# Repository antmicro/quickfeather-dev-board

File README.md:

# QuickFeather Development Board

Copyright (c) 2019-2024 [Antmicro](https://www.antmicro.com)

## Overview

This project contains open hardware design files for the [QuickFeather development board](https://www.quicklogic.com/products/eos-s3/quickfeather-development-kit/) based on the QuickLogic [EOS S3 Sensor Processing Platform](https://www.quicklogic.com/products/eos-s3/).
The design files were created by [Antmicro](https://www.antmicro.com) in cooperation with [QuickLogic](https://www.quicklogic.com/).
The board has been designed to keep compatibility with the [Adafruit Feather](https://learn.adafruit.com/adafruit-feather/feather-specification) ecosystem of evaluation boards.
This allows the user to explore functionalities of the EOS S3 platform.

### Project structure:

The main directory contains the KiCad design files, LICENSE and README.
The remaining files are stored in the following directories:

* ``img`` - contains graphics for this README
* ``doc`` - contains generated schematics and other documentation
* ``lib`` - contains KiCad component library

## Key features

* QuickLogic EOS S3 Processing Platform
* [mCube MC3635](https://www.memsic.com/Public/Uploads/uploadfile/files/20220119/MC3635Datasheet.pdf) accelerometer
* [Infineon DPS310](https://www.infineon.com/dgdl/Infineon-DPS310-DataSheet-v01_01-EN.pdf?fileId=5546d462576f34750157750826c42242) pressure sensor
* [Infineon IM69D130](https://www.infineon.com/dgdl/Infineon-IM69D130-DS-v01_00-EN.pdf?fileId=5546d462602a9dc801607a0e46511a2e) MEMS microphone 
* 16Mbit of on-board [flash memory](https://www.gigadevice.com.cn/Public/Uploads/uploadfile/files/20220714/DS-00086-GD25Q16C-Rev3.2.pdf)
* User button and RGB LED
* Powered from USB or a single Li-Po battery
* Integrated [battery charger](http://ww1.microchip.com/downloads/en/DeviceDoc/20001984g.pdf)
* USB data signals tied to programmable logic
* IO signals break-routed into general purpose pinheads
* Compatible with standard 0.1" breadboards

## Development ecosystem

### Simulation

The board is supported in [Renode](https://renode.io/), the open source simulation framework by Antmicro - you can run a virtual copy of this hardware for software development purposes on your PC. A link to the relevant demo script is provided in Renode's [supported boards section](https://renode.readthedocs.io/en/latest/introduction/supported-boards.html).

## License

This project is licensed under the [CC BY-SA 4.0 DEED](LICENSE) license.

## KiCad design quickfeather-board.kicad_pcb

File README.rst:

==============================
QuickFeather Development Board
==============================

Copyright (c) 2019-2021 `Antmicro <https://www.antmicro.com>`_

.. figure:: img/feather-board.png

Overview
========

This repository contains open hardware design files for the `QuickFeather development board <https://www.quicklogic.com/products/eos-s3/quickfeather-development-kit/>`_ based on the QuickLogic `EOS S3 Sensor Processing Platform <https://www.quicklogic.com/products/eos-s3/>`_.
The design files were created by `Antmicro <https://www.antmicro.com>`_ in cooperation with `QuickLogic <https://www.quicklogic.com/>`_.
The board has been designed to keep compatibility with the `Adafruit Feather <https://learn.adafruit.com/adafruit-feather/feather-specification>`_ ecosystem of evaluation boards.
This allows the user to explore functionalities of the EOS S3 platform.

Key features
------------

* QuickLogic EOS S3 Processing Platform
* `mCube MC3635 <https://mcubemems.com/wp-content/uploads/2019/06/MC3635-Datasheet-APS-048-0044v1.6.pdf>`_ accelerometer
* `Infineon DPS310 <https://www.infineon.com/dgdl/Infineon-DPS310-DataSheet-v01_01-EN.pdf?fileId=5546d462576f34750157750826c42242>`_ pressure sensor
* `Infineon IM69D130 <https://www.infineon.com/dgdl/Infineon-IM69D130-DS-v01_00-EN.pdf?fileId=5546d462602a9dc801607a0e46511a2e>`_ MEMS microphone 
* 16Mbit of on-board `flash memory  <http://www.gigadevice.com/datasheet/gd25q16c/>`_
* User button and RGB LED
* Powered from USB or a single Li-Po battery
* Integrated `battery charger <http://ww1.microchip.com/downloads/en/DeviceDoc/20001984g.pdf>`_
* USB data signals tied to programmable logic
* IO signals break-routed into general purpose pinheads
* Compatible with standard 0.1" breadboards

Layout and dimensions
---------------------

.. figure:: img/feather-layout.png

Development ecosystem
=====================

Simulation
----------

The board is supported in `Renode <https://renode.io/>`_, the open source simulation framework by Antmicro - you can run a virtual copy of this hardware for software development purposes on your PC. A link to the relevant demo script is provided in Renode's `supported boards section <https://renode.readthedocs.io/en/latest/introduction/supported-boards.html>`_.

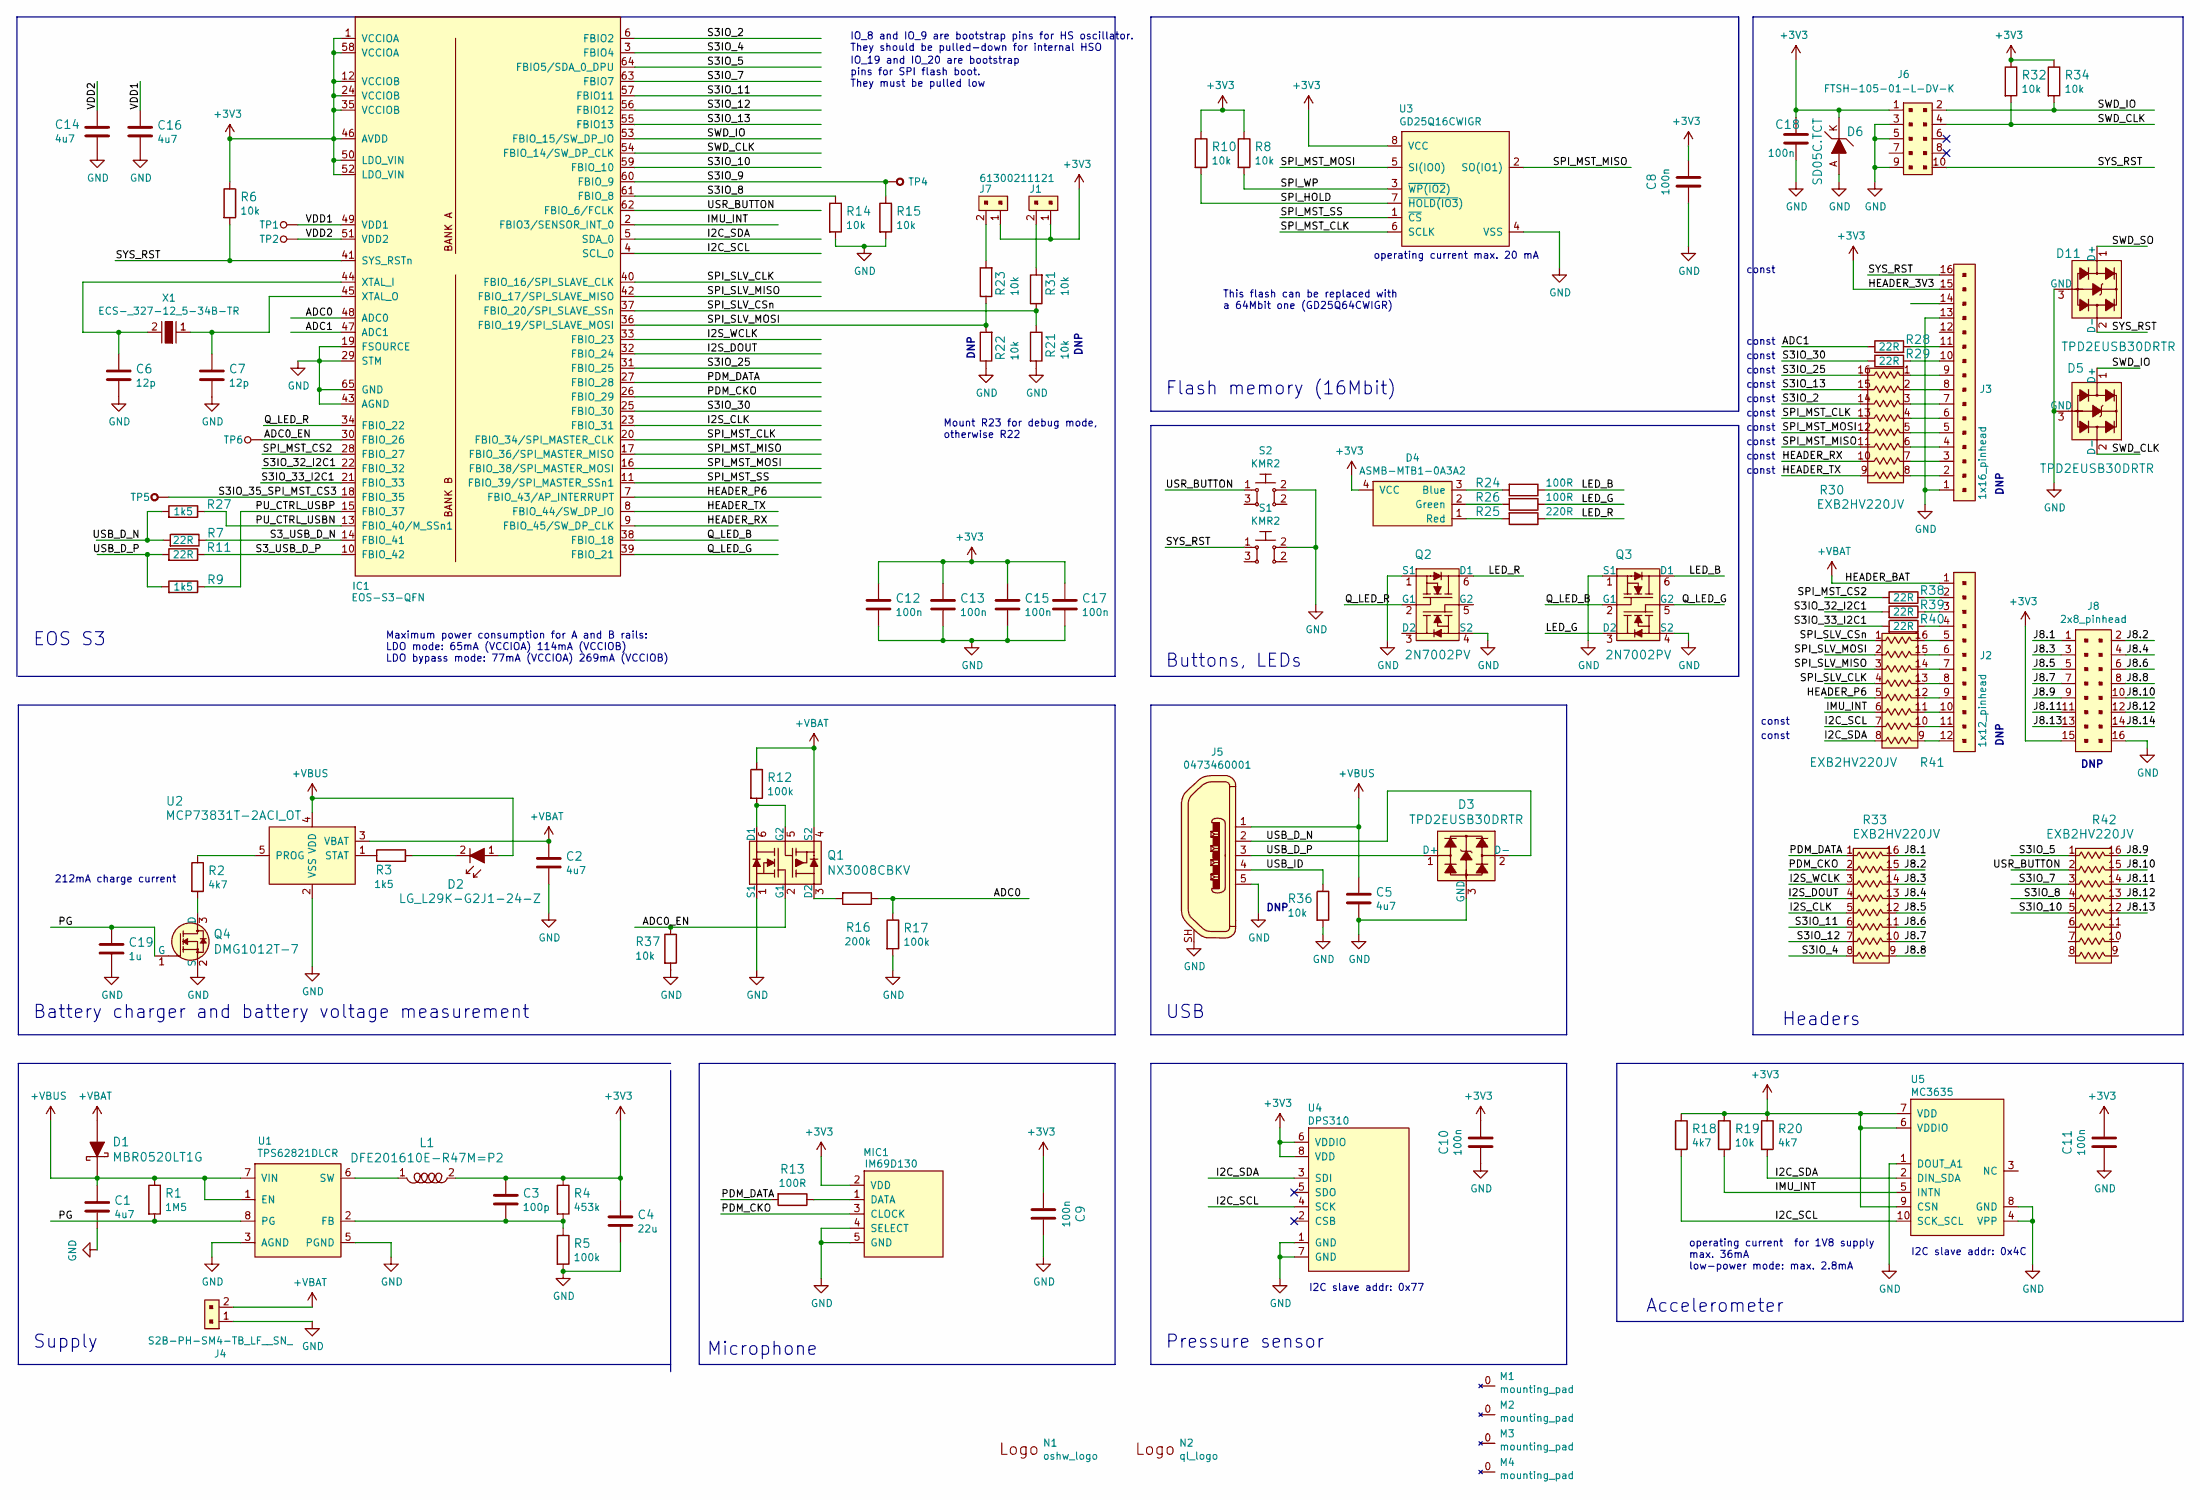
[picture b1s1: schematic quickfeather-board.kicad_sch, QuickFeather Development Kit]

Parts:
C1, C2, C5, C14, C16: C_4u7_0603; 0603-cap; MPN C1608X5R1V475M080AC
C3: C_100p_0402; 0402-cap; MPN 0402N101J500CT
C4: C_22u_0603; 0603-cap; MPN GRM188R60J226MEA0D
C6, C7: C_12p_0402; 0402-cap; MPN CGA2B2C0G1H120J050BA
C8, C9, C10, C11, C12, C13, C15, C17, C18: C_100n_0402_6V3; 0402-cap; MPN 0402X104K6R3CT
C19: C_1u_0402; 0402-cap; MPN C1005X6S1A105K050BC
D1: MBR0520LT1G; SOD-123; MPN MBR0520LT1G
D2: LG_L29K-G2J1-24-Z; LED_0603; MPN LG L29K-G2J1-24-Z
D3, D5, D11: TPD2EUSB30DRTR; SOT-3; MPN TPD2EUSB30DRTR
D4: ASMB-MTB1-0A3A2; LED-PLCC4_3.2x2.8mm_B; MPN UHD1110-FKA
D6: SD05C.TCT; SOD-323-SD05; MPN SD05C.TCT
IC1: EOS-S3-QFN; QFN-64_8.5x8.5_EOS; MPN EOSA1-S-PUN64
J1, J7: 61300211121; PinHeader_1x2_P2.54_Drill0.9mm; MPN 61300211121
J2: 1x12_pinhead; MPN MC34733
J3: 1x16_pinhead; MPN 61301611121
J4: S2B-PH-SM4-TB_LF__SN_; PinHeader_2x1mm_P2mm_SMD_RA; MPN S2B-PH-SM4-TB(LF)(SN)
J5: 0473460001; USB_Micro_B_Female_0473460001; MPN 0473460001
J6: FTSH-105-01-L-DV-K; PinHeader_2x5_P1.27_SMD; MPN FTSH-105-01-L-DV-K
J8: 2x8_pinhead; MPN 2213S-16G
L1: DFE201610E-R47M=P2; 0806; MPN DFE201610E-R47M=P2
M1, M2, M3, M4: mounting_pad; MPAD
MIC1: IM69D130; MPN IM69D130
N1: oshw_logo; oshw-logo
N2: ql_logo; LOGO
Q1: NX3008CBKV; SOT-563; MPN NX3008CBKV
Q2, Q3: 2N7002PV; SOT-563; MPN 2N7002PV
Q4: DMG1012T-7; SOT-523; MPN DMG1012T-7
R1: R_1M5_0402; 0402-res; MPN MCWR04W1504FTL
R2, R18, R20: R_4k7_0402; 0402-res; MPN ERJ2GEJ472X
R3, R9, R27: R_1k5_0402; 0402-res; MPN ERJ2RKF1501X
R4: R_453k_0402; 0402-res; MPN CRCW0402453KFKED
R5, R12, R17: R_100k_0402; 0402-res; MPN CRCW0402100KFKEDHP
R6, R8, R10, R14, R15, R19, R21, R22, R23, R31, R32, R34, R36, R37: R_10k_0402; 0402-res; MPN CRCW040210K0FKEDHP
R7, R11, R28, R29, R38, R39, R40: R_22R_0402; 0402-res; MPN CRCW040222R0FKED
R13, R24, R26: R_100R_0402; 0402-res; MPN CR0402-FX-1000GLF
R16: R_200k_0402; 0402-res; MPN RC0402FR-07200KL
R25: R_220R_0402; 0402-res; MPN RMCF0402JT220R
R30, R33, R41, R42: EXB2HV220JV; R_Array_Convex_8x0602; MPN EXB2HV220JV
S1, S2: KMR2; SW_SPST_4.2x2.8; MPN KMR211NGLFS
TP1, TP2, TP6: TP_SMD1MM; Testpoint_smd_1mm; MPN N/A
TP4, TP5: TP_THT; Testpoint_THT_Drill0.9mm; MPN N/A
U1: TPS62821DLCR; QFN-8_2x1mm; MPN TPS62821DLCR
U2: MCP73831T-2ACI_OT; SOT-753; MPN MCP73831T-2ACI/OT
U3: GD25Q16CWIGR; GD25Q16CWIG; MPN GD25Q16CWIGR
U4: DPS310; PG-VLGA-8-2; MPN DPS310
U5: MC3635; MPN MC3635
X1: ECS-_327-12_5-34B-TR; SMD-2_3.2x1.5mm; MPN ECS-.327-12.5-34B-TR

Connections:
+3V3: C3.1, C4.1, C8.1, C9.2, C10.1, C11.1, C12.1, C13.1, C15.1, C17.1, C18.1, D4.4 (VCC), D6.K, IC1.1 (VCCIOA), IC1.12 (VCCIOB), IC1.24 (VCCIOB), IC1.35 (VCCIOB), IC1.46 (AVDD), IC1.50 (LDO_VIN), IC1.52 (LDO_VIN), IC1.58 (VCCIOA), J1.1, J3.15, J6.1, J7.1, J8.15, L1.2, MIC1.2 (VDD), R4.1, R6.1, R8.1, R10.1, R18.1, R19.1, R20.1, R32.1, R34.1, U3.8 (VCC), U4.6 (VDDIO), U4.8 (VDD), U5.6 (VDDIO), U5.7 (VDD), U5.9 (CSN)
+VBAT: C2.1, D1.A, J2.1, J4.2, Q1.4 (S2), R12.1, U2.3 (VBAT)
+VBUS: C1.1, C5.1, D1.K, D2.1, J5.1, R1.1, U1.1 (EN), U1.7 (VIN), U2.4 (VDD)
/ADC0: IC1.48 (ADC0), R16.1, R17.1
/ADC0_EN: IC1.30 (FBIO_26), Q1.2 (G1), R37.1, TP6.1
/ADC1: IC1.47 (ADC1), R28.1
/HEADER_P6: IC1.7 (FBIO_43/AP_INTERRUPT), R41.5
/HEADER_RX: IC1.9 (FBIO_45/SW_DP_CLK), R30.10
/HEADER_TX: IC1.8 (FBIO_44/SW_DP_IO), R30.9
/I2C_SCL: IC1.4 (SCL_0), R18.2, R41.7, U4.4 (SCK), U5.10 (SCK_SCL)
/I2C_SDA: IC1.5 (SDA_0), R20.2, R41.8, U4.3 (SDI), U5.2 (DIN_SDA)
/I2S_CLK: IC1.23 (FBIO_31), R33.5
/I2S_DOUT: IC1.32 (FBIO_24), R33.4
/I2S_WCLK: IC1.33 (FBIO_23), R33.3
/IMU_INT: IC1.2 (FBIO3/SENSOR_INT_0), R19.2, R41.6, U5.5 (INTN)
/J8.1: J8.1, R33.16
/J8.2: J8.2, R33.15
/J8.3: J8.3, R33.14
/J8.4: J8.4, R33.13
/J8.5: J8.5, R33.12
/J8.6: J8.6, R33.11
/J8.7: J8.7, R33.10
/J8.8: J8.8, R33.9
/J8.9: J8.9, R42.16
/J8.10: J8.10, R42.15
/J8.11: J8.11, R42.14
/J8.12: J8.12, R42.13
/J8.13: J8.13, R42.12
/J8.14: J8.14
/LED_B: Q3.6 (D1), R24.1
/LED_G: Q3.3 (D2), R26.1
/LED_R: Q2.6 (D1), R25.1
/PDM_CKO: IC1.26 (FBIO_29), MIC1.3 (CLOCK), R33.2
/PDM_DATA: IC1.27 (FBIO_28), R13.2, R33.1
/PG: C19.1, Q4.1 (G), R1.2, U1.8 (PG)
/PU_CTRL_USBN: IC1.13 (FBIO_40/M_SSn1), R27.1
/PU_CTRL_USBP: IC1.15 (FBIO_37), R9.1
/Q_LED_B: IC1.38 (FBIO_18), Q3.2 (G1)
/Q_LED_G: IC1.39 (FBIO_21), Q3.5 (G2)
/Q_LED_R: IC1.34 (FBIO_22), Q2.2 (G1)
/S3IO_2: IC1.6 (FBIO2), R30.14
/S3IO_4: IC1.3 (FBIO4), R33.8
/S3IO_5: IC1.64 (FBIO5/SDA_0_DPU), R42.1
/S3IO_7: IC1.63 (FBIO7), R42.3
/S3IO_8: IC1.61 (FBIO_8), R14.1, R42.4
/S3IO_9: IC1.60 (FBIO_9), R15.1, TP4.1
/S3IO_10: IC1.59 (FBIO_10), R42.5
/S3IO_11: IC1.57 (FBIO11), R33.6
/S3IO_12: IC1.56 (FBIO12), R33.7
/S3IO_13: IC1.55 (FBIO13), R30.15
/S3IO_25: IC1.31 (FBIO_25), R30.16
/S3IO_30: IC1.25 (FBIO_30), R29.1
/S3IO_32_I2C1: IC1.22 (FBIO_32), R39.2
/S3IO_33_I2C1: IC1.21 (FBIO_33), R40.2
/S3IO_35_SPI_MST_CS3: IC1.18 (FBIO_35), TP5.1
/S3_USB_D_N: IC1.14 (FBIO_41), R7.1
/S3_USB_D_P: IC1.10 (FBIO_42), R11.1
/SPI_HOLD: R10.2, U3.7 (~HOLD(IO3))
/SPI_MST_CLK: IC1.20 (FBIO_34/SPI_MASTER_CLK), R30.13, U3.6 (SCLK)
/SPI_MST_CS2: IC1.28 (FBIO_27), R38.2
/SPI_MST_MISO: IC1.17 (FBIO_36/SPI_MASTER_MISO), R30.11, U3.2 (SO(IO1))
/SPI_MST_MOSI: IC1.16 (FBIO_38/SPI_MASTER_MOSI), R30.12, U3.5 (SI(IO0))
/SPI_MST_SS: IC1.11 (FBIO_39/SPI_MASTER_SSn1), U3.1 (~CS)
/SPI_SLV_CLK: IC1.40 (FBIO_16/SPI_SLAVE_CLK), R41.4
/SPI_SLV_CSn: IC1.37 (FBIO_20/SPI_SLAVE_SSn), R21.1, R31.1, R41.1
/SPI_SLV_MISO: IC1.42 (FBIO_17/SPI_SLAVE_MISO), R41.3
/SPI_SLV_MOSI: IC1.36 (FBIO_19/SPI_SLAVE_MOSI), R22.2, R23.1, R41.2
/SPI_WP: R8.2, U3.3 (~WP(IO2))
/SWD_CLK: D5.2 (D-), IC1.54 (FBIO_14/SW_DP_CLK), J6.4, R32.2
/SWD_IO: D5.1 (D+), IC1.53 (FBIO_15/SW_DP_IO), J6.2, R34.2
/SWD_SO: D11.1 (D+)
/SYS_RST: D11.2 (D-), IC1.41 (SYS_RSTn), J3.16, J6.10, R6.2, S1.1
/USB_D_N: D3.2 (D-), J5.2, R7.2, R27.2
/USB_D_P: D3.1 (D+), J5.3, R9.2, R11.2
/USB_ID: J5.4, R36.1
/USR_BUTTON: IC1.62 (FBIO_6/FCLK), R42.2, S2.1
/VDD1: C16.1, IC1.49 (VDD1), TP1.1
/VDD2: C14.1, IC1.51 (VDD2), TP2.1
GND: C1.2, C2.2, C4.2, C5.2, C6.2, C7.2, C8.2, C9.1, C10.2, C11.2, C12.2, C13.2, C14.2, C15.2, C16.2, C17.2, C18.2, C19.2, D3.3 (GND), D5.3 (GND), D6.A, D11.3 (GND), IC1.19 (FSOURCE), IC1.29 (STM), IC1.43 (AGND), IC1.65 (GND), J3.1, J3.13, J4.1, J5.5, J5.SH, J6.3, J6.5, J6.9, J8.16, MIC1.4 (SELECT), MIC1.5 (GND), Q1.1 (S1), Q2.1 (S1), Q2.4 (S2), Q3.1 (S1), Q3.4 (S2), Q4.2 (S), R5.2, R14.2, R15.2, R17.2, R21.2, R22.1, R36.2, R37.2, S1.2, S2.2, U1.3 (AGND), U1.5 (PGND), U2.2 (VSS), U3.4 (VSS), U4.1 (GND), U4.7 (GND), U5.1 (DOUT_A1), U5.4 (VPP), U5.8 (GND)
unnamed: C3.2, R4.2, R5.1, U1.2 (FB)
unnamed: C6.1, IC1.44 (XTAL_I), X1.2
unnamed: C7.1, IC1.45 (XTAL_O), X1.1
unnamed: D2.2, R3.1
unnamed: D4.1 (Red), R25.2
unnamed: D4.2 (Green), R26.2
unnamed: D4.3 (Blue), R24.2
unnamed: J1.2, R31.2
unnamed: J2.2, R38.1
unnamed: J2.3, R39.1
unnamed: J2.4, R40.1
unnamed: J2.5, R41.16
unnamed: J2.6, R41.15
unnamed: J2.7, R41.14
unnamed: J2.8, R41.13
unnamed: J2.9, R41.12
unnamed: J2.10, R41.11
unnamed: J2.11, R41.10
unnamed: J2.12, R41.9
unnamed: J3.2, R30.8
unnamed: J3.3, R30.7
unnamed: J3.4, R30.6
unnamed: J3.5, R30.5
unnamed: J3.6, R30.4
unnamed: J3.7, R30.3
unnamed: J3.8, R30.2
unnamed: J3.9, R30.1
unnamed: J3.10, R29.2
unnamed: J3.11, R28.2
unnamed: J7.2, R23.2
unnamed: L1.1, U1.6 (SW)
unnamed: MIC1.1 (DATA), R13.1
unnamed: Q1.3 (D2), R16.2
unnamed: Q1.5 (G2), Q1.6 (D1), R12.2
unnamed: Q4.3 (D), R2.2
unnamed: R2.1, U2.5 (PROG)
unnamed: R3.2, U2.1 (STAT)

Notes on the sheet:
Battery charger and battery voltage measurement
const
Pressure sensor
DNP
operating current max. 20 mA
USB
IO_19 and IO_20 are bootstrap pins for SPI flash boot. They must be pulled low
Supply
Microphone
Headers
This flash can be replaced with a 64Mbit one (GD25Q64CWIGR)
212mA charge current
EOS S3
I2C slave addr: 0x4C
I2C slave addr: 0x77
Flash memory (16Mbit)
Buttons, LEDs
Mount R23 for debug mode, otherwise R22
Maximum power consumption for A and B rails: LDO mode: 65mA (VCCIOA) 114mA (VCCIOB) LDO bypass mode: 77mA (VCCIOA) 269mA (VCCIOB)
IO_8 and IO_9 are bootstrap pins for HS oscillator. They should be pulled-down for internal HSO
Accelerometer
operating current for 1V8 supply max. 36mA low-power mode: max. 2.8mA

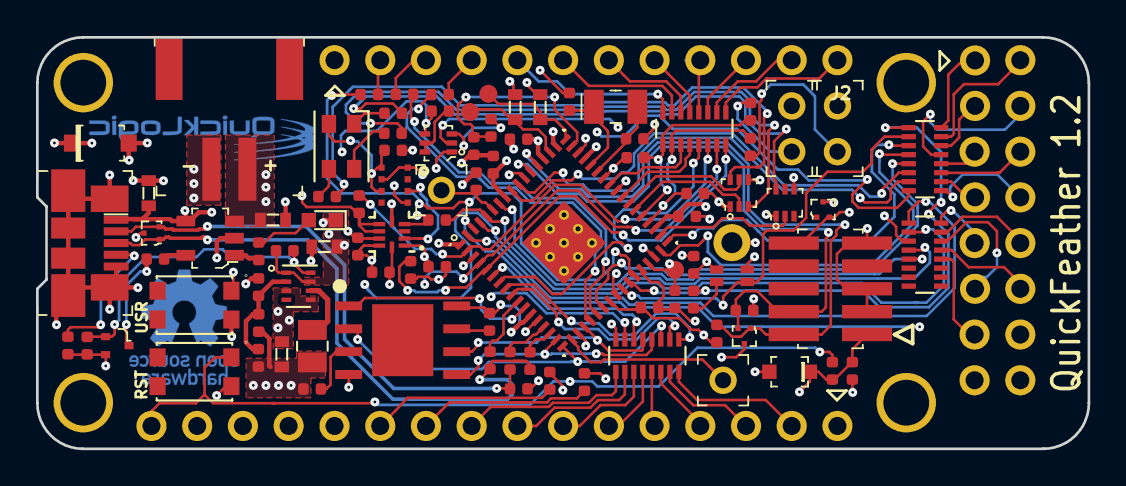
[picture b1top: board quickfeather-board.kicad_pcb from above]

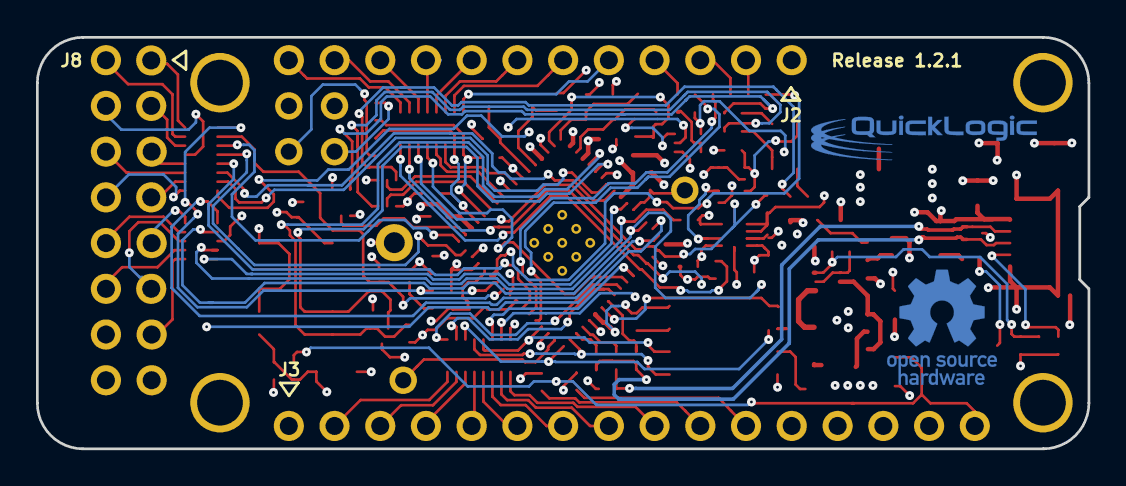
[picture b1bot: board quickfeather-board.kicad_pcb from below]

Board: 4 copper layers, 58.4 x 22.9 mm, 101 parts (2 on the bottom side), 114 nets.

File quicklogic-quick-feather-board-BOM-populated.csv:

Reference,Quantity,Value,Footprint,Manufacturer,MPN,
C1 C14 C16 C2 C5,5,C_4u7_0603,0603-cap,TDK,C1608X5R1V475M080AC,
C10 C11 C12 C13 C15 C17 C18 C8 C9,9,C_100n_0402_6V3,0402-cap,Walsin,0402X104K6R3CT,
C3,1,C_100p_0402,0402-cap,WALSIN,0402N101J500CT,
C4,1,C_22u_0603,0603-cap,MURATA,GRM188R60J226MEA0D,
C6 C7,2,C_12p_0402,0402-cap,TDK,CGA2B2C0G1H120J050BA,
D1,1,MBR0520LT1G,SOD-123,ON Semiconductor,MBR0520LT1G,
D11 D3 D5,3,TPD2EUSB30DRTR,SOT-3,Texas Instruments,TPD2EUSB30DRTR,
D2,1,LG_L29K-G2J1-24-Z,LED_0603,OSRAM Opto Semiconductors Inc.,LG L29K-G2J1-24-Z,
D4,1,ASMB-MTB1-0A3A2,LED-PLCC4_3.2x2.8mm_B,Broadcom,ASMB-MTB1-0A3A2,
D6,1,SD05C.TCT,SOD-323-SD05,Semtec,SD05C.TCT,
IC1,1,EOS-S3-QFN,QFN-64_8.5x8.5_EOS,,,Delivered by Quicklogic
J1 J7,2,61300211121,PinHeader_1x2_P2.54_Drill0.9mm,Wurth Electronic,61300211121,
J4,1,S2B-PH-SM4-TB_LF__SN_,PinHeader_2x1mm_P2mm_SMD_RA,JST Sales America Inc.,S2B-PH-SM4-TB(LF)(SN),
J5,1,473460001,USB_Micro_B_Female_0473460001,Molex,473460001,
J6,1,FTSH-105-01-L-DV-K,PinHeader_2x5_P1.27_SMD,Samtec Inc.,FTSH-105-01-L-DV-K,
L1,1,DFE201610E-R47M=P2,0805-res,Murata,DFE201610E-R47M=P2,
MIC1,1,IM69D130,IM69D130,Infineon,IM69D130,
Q1,1,NX3008CBKV,SOT-563,Nexperia,NX3008CBKV,
Q2 Q3,2,2N7002PV,SOT-563,Nexperia,2N7002PV,
R1 R12 R17 R5,4,R_100k_0402,0402-res,VISHAY,CRCW0402100KFKEDHP,
R10 R14 R15 R19 R23 R31 R32 R34 R37 R6 R8,11,R_10k_0402,0402-res,VISHAY,CRCW040210K0FKEDHP,
R11 R28 R29 R38 R39 R40 R7,7,R_22R_0402,0402-res,VISHAY,CRCW040222R0FKED,
R13 R24 R26,3,R_100R_0402,0402-res,BOURNS,CR0402-FX-1000GLF,
R16,1,R_200k_0402,0402-res,YAGEO_(PHYCOMP),RC0402FR-07200KL,
R18 R2 R20,3,R_4k7_0402,0402-res,PANASONIC_ELECTRONIC_COMPONENTS,ERJ2GEJ472X,
R25,1,R_220R_0402,0402-res,TE_CONNECTIVITY_/_NEOHM,CRG0402J220R,
R3 R9,2,R_1k5_0402,0402-res,PANASONIC_ELECTRONIC_COMPONENTS,ERJ2RKF1501X,
R30 R33 R41,3,EXB2HV220JV,R_Array_Convex_8x0602,Panasonic,EXB2HV220JV,
R4,1,R_453k_0402,0402-res,VISHAY,CRCW0402453KFKED,
S1 S2,2,KMR2,SW_SPST_4.2x2.8,C&K Components,KMR211NGLFS,
U1,1,TPS62821DLCR,QFN-8_2x1mm,Texas Instruments,TPS62821DLCR,
U2,1,MCP73831T-2ACI_OT,SOT-753,Microchip Technology,MCP73831T-2ACI/OT,
U3,1,GD25Q16CWIGR,GD25Q16CWIG,GigaDevice,GD25Q16CWIGR,
U4,1,DPS310,PG-VLGA-8-2,Infineon,DPS310,
U5,1,MC3635,MC3635,mCube,MC3635,
X1,1,ECS-_327-12_5-34B-TR,SMD-2_3.2x1.5mm,ECS Inc.,ECS-.327-12.5-34B-TR,

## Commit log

2019-11-05 added project files, board file with defined outline
2020-02-13 Added power supply circuits
2020-02-13 Updated notes on schematic
2020-02-13 Added flash memory and 32kHz crystal
2020-02-13 Added gitignore
2020-02-13 Added README
2020-02-13 Added gerbers for initial pcb technological analysis
2020-02-13 Updated design rules, proposed initial package escape for 42-WLCSP
2020-02-13 Updated package escape so we are loosing 1 ball of WLCSP
2020-02-13 Added net names to EOS-S3 pins
2020-02-13 Updated .gitignore, updated board title
2020-02-13 Added IM69D130 microphone to schematics
2020-02-13 Package escape implemented with stacked vias
2020-02-13 Changed flash memory, connected missing nets, cleanup
2020-02-13 Board stackup changed to 6L, added GND+PWR plane
2020-02-13 Added README files
2020-02-13 Added TVS for USB
2020-02-13 Added OSHW logotypes
2020-02-13 Added pressure sensor
2020-02-13 Added power rail symbols
2020-02-13 Added license
2020-02-13 Updated internal library
2020-02-13 Updated library connections
2020-02-13 Added accelerometer and circuit for measuring battery voltage
2020-02-13 Added bootstrap resistors, connected pressure sensor to I2C bus, placed components on PCB
2020-02-13 Added BTN/LED section
2020-02-13 Design updated after internal review
2020-02-13 Updated naming
2020-02-13 Added schematic PDF
2020-02-13 Updated 3DVis
2020-02-13 Added remarks about power consuption, added filtering capactitors for EOS-S3
2020-02-13 Added TBDs to schematics
2020-02-13 Updated schematic annotation
2020-02-13 Changes to header, tweaks to LED, added BAT connector
2020-02-13 Added pinhead connectors for debug and programming
2020-02-13 Added BOM
2020-02-13 Updated PDF schematics
2020-02-13 Added LED driving transistors
2020-02-13 Removed prototyping area, updated component placement
2020-02-13 Updated 3D models
2020-02-13 J2 and J3 flipped to match feather-like pinouts
2020-02-13 Changed MPN for buttons, updated 3D models
2020-02-13 Rearranged component placement
2020-02-13 Finished component placement
2020-02-13 Updated 3D vis
2020-02-13 Updated PDF with schematic, updated BOM
2020-02-13 Updated component placement, added 3D models for pin headers
2020-02-13 Routing almost finished
2020-02-13 Added a 2-pin header to configure bootstrap pins for EOS IC
2020-02-13 Removed HEADER_A5 connection to J6, removed R31 and R33
2020-02-13 Added some MPNs to libraries and updated them on schematic, updated BOM and schematic PDF
2020-02-13 Placement proposal
2020-02-13 Updated PDF schematics and 3D vis
2020-02-13 Updated component definitions on PCB
2020-02-13 R22 marked as DNP
2020-02-13 Added connection between USB_ID and HEADER_A5
2020-02-13 Changed jumper to mini jumper + slide switch. Footprint update
2020-02-13 Fixed BOM
2020-02-13 Added 3D vis of bottom side
2020-02-13 Connected IMU_INT to IC1 C7 pin
2020-02-13 Fixed DRC issues, updated layout
2020-02-13 EOS-S3 changed to QFN version
2020-02-13 Component placement refined after pinout changes
2020-02-13 Added J8 connector, extended board outline
2020-02-13 Early attempt of routing of most crossed lines
2020-02-13 Swapped signals connected to EOS S3 pin 27 and 28
2020-02-13 Added pin 1 indicators for all ICs
2020-02-13 Added gerbers used for making prototypes in rev. 1.0
2020-02-13 Added MPNs for pinheads, updated BOM and schematic PDF
2020-02-13 Corrected MPN for pinhead
2020-02-13 Fixed SOT-563 footprint
2020-02-13 Moved J8 to match 2.54mm grid
2020-02-13 Improved layout around DC/DC converter, added logotypes
2020-02-13 Added production docs (BOM, PnP)
2020-02-13 Minor updates
2020-02-13 Updated footprint for RGB LED. Project revision changed to 1.0.1
2020-02-13 BOM optimized
2020-02-13 Updated schematic PDF
2020-02-13 Updated DFE2016 footprint and 3D model
2020-02-13 Minor fix in PCB file
2020-02-13 Introduced virtual components, marked pinheads as DNP
2020-02-13 Modified MC3635 paste layer pattern, tweaked layout around MC3635
2020-02-13 Documentation used for EMS analysis
2020-02-13 Updated MPN for 220R, updated BOM
2020-02-13 Added 3D models to resistor arrays
2020-02-13 Updated schematic notes
2020-02-13 Added information about flash memory size
2020-02-13 Updated production files for revision 1.1
2020-02-13 Minor fixes
2020-02-13 Cleanup, simplified file naming
2020-02-13 Re-generated production files
2020-02-13 Added 3D model
2020-02-13 Updated STL model
2020-02-13 Minor fix
2020-03-06 Added delayed start circuit to battery charger
2020-03-06 Updated library references
2020-03-06 Updated PCB layout for charger with delayed startup
2020-03-06 BOM and internal library updated
2020-03-06 Updated manufacturing documentation
2020-03-12 Added board pins description and drawings
2020-03-13 Corrected IO_27 to IO_30
2020-03-27 Added plots for fabrication layers
2020-03-27 Added description for PCB finish
2020-03-27 Updated fabrication notes
2020-03-28 MInor review of README
2020-03-28 Fix QuickLogic capitalization
2020-03-28 Add mention of Renode
2020-03-28 Add link to the QF devboard on QL website
2020-03-28 Update naming convention
2020-03-28 Add MPNs to peripheral components listed in README
2020-03-31 Add board name to TOP silkscreen
2020-03-31 Update 3D vis
2020-03-31 Add black soldermask to 3D Vis
2020-03-31 Minor change
2020-04-01 Add 3D stl model
2020-05-07 Add release 1.2.0
2020-05-07 Update Schematic PDF
2020-05-12 Add release 1.2.1
2020-05-12 Remove redundant model
2020-05-13 Add pos files for PickNPlace
2020-05-14 Update IM69D130 and PG-VLGA-8-2
2020-05-14 Move pos files to doc
2020-05-18 Make 3D Vis larger
2020-05-21 Update IC1 pin names
2021-05-03 README: add copyrights
2023-08-07 Notes added by 'git notes add'
2024-02-08 [#54927] Update to KiCad7
2024-02-08 [#54927] Globlib
2024-02-08 [#54927] Update Flash memory
2024-02-08 [#54927] Standardize USER IO
2024-02-16 [#54927] Standardize Microphone and USB connectors
2024-02-16 [#54927] Standardize Accelerometer and pressure sensor
2024-02-16 [#54927] Standardize battery charger
2024-02-16 [#54927] Standardize headers
2024-02-16 [#54927] Add buses
2024-02-16 [#54927] Standardize supply
2024-02-16 [#54927] Standardize EOS 3S
2024-02-16 [#54927] Update J4
2024-02-16 [#54927] Minor graphical updates
2024-02-16 [#54927] Update components on PCB to standardized versions
2024-02-16 [#54927] Update 2x8 pin header
2024-02-16 [#54927] Hide designators
2024-02-16 [#54927] Update X1
2024-02-16 [#54927] Fix DRC
2024-02-16 [#54927] Update U1, U3, U5
2024-02-16 [#54927] Fix ERC
2024-02-16 [#54927] Loclib
2024-02-16 [#54927] Update symbols
2024-02-16 [#54927] Add mounting holes
2024-02-16 [#54927] Clear DRC
2024-02-16 [#54927] Update components
2024-02-16 [#54927] Update QFN blend file
2024-02-16 [#54927] Change IC1 to U6
2024-02-16 [#54927] Fix DNP
2024-02-16 [#54927] Center IM69D130
2024-02-16 [#54927] Fix 3d model of 1x16 pin head
2024-02-16 [#54927] Change QFN-64 footprint name
2024-02-16 [#54927] Fix silkscreen
2024-02-16 [#54927] Convert README to MD, update board image, fix links
2024-02-20 [#54927] Add OHP assets
